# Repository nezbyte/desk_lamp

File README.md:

# desk_lamp
 FPGA based desk lamp upgrade

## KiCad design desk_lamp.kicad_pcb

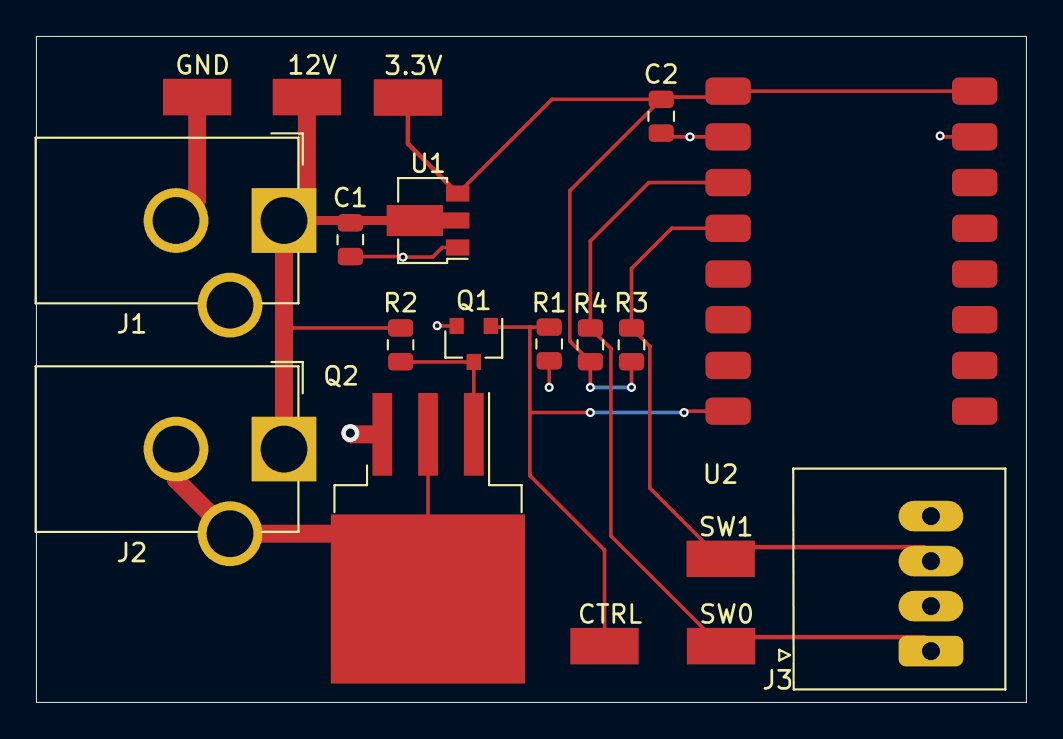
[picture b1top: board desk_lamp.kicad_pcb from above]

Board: 2 copper layers, 55.0 x 37.0 mm, 19 parts (0 on the bottom side), 8 nets.

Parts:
C1, C2: 100n; C_0805_2012Metric
J1, J2: CON-SOCJ-2155; BarrelJack_CUI_PJ-102AH_Horizontal
J3: Phoenix_Contact_1989764; PhoenixContact_PTSA_0,5_4-2,5-F_P2.50mm_Horizontal
Q1: 2N7002K; SOT-23
Q2: MCB150N06YB-TP; TO-263-3_TabPin2
R1, R2, R3, R4: 10k; R_0805_2012Metric
TP1: 12V; TestPoint_5019
TP2: GND; TestPoint_5019
TP3: SW0; TestPoint_5019
TP4: SW1; TestPoint_5019
TP5: CTRL; TestPoint_5019
TP6: 3.3V; TestPoint_5019
U1: MCP1703T-3302E/MB; SOT-89-3
U2: ICE30LP384_QFN32_MODULE

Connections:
+3V3: C2.1, R3.1, R4.1, TP6.1, U1.3, U2.1, U2.16
+12V: C1.1, J1.1, J2.1, R2.1, TP1.1, U1.2
GND: C1.2, C2.2, J1.2, J1.3, J3.2, J3.4, Q1.2, Q2.3, R1.2, TP2.1, U1.1, U2.2, U2.15
I_SW0: J3.1, R4.2, TP3.1, U2.3
I_SW1: J3.3, R3.2, TP4.1, U2.4
Lamp_Control: Q1.1, R1.1, TP5.1, U2.8
unnamed: J2.2, J2.3, Q2.2
unnamed: Q1.3, Q2.1, R2.2

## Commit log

2020-09-18 Add kicad gitignore
2020-09-18 Add kicad files
2020-09-18 added gerbers
2020-09-18 updated gitignore; adding BOM and GBRs
2020-10-05 Fixed mosfet swapped pins
    Gate and Drain pins were swapped.
2020-10-05 Resized barrel jack connector holes
    Barrel jack connector holes were found to be too small to fit component. Updated footprint and layout to accomodate larger holes.
2020-10-06 Corrected TCXO and 3V3 LDO
    TCXO was replaced with 25MHz that is no longer 0.8Vpp.
    LDO did not match footprint. Replaced with compatible model that matched fabbed footprint.
    Gerbers updated and could be sent to fab house if desired.
2020-10-06 Switched to FPGA module
    Switched to FPGA module to make changes easier going forward.
